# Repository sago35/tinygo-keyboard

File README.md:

# USB HID Keyboard firmware for TinyGo

**The API is not yet fixed.**  

The following are supported.  

* key input
    * squared matrix scan
    * matrix scan
    * duplex-matrix scan
    * rotary encoder
    * GPIO
    * UART
    * Shifter (tinygo.org/x/drivers/shifter)
* layer feature by mod key
* mouse click / mouse wheel
* support TRRS (UART)
* support [Vial](https://vial.rocks/)
    * Keymap
    * [Layers](https://get.vial.today/manual/layers.html) (MO(x), TO(x))
    * Matrix testers
    * [Macros](https://get.vial.today/manual/macros.html)
    * [Mod-Tap](https://docs.qmk.fm/mod_tap)
    * [Modifier Keys](https://docs.qmk.fm/feature_advanced_keycodes#modifier-keys)
    * [Combos](https://get.vial.today/manual/combos.html)

## Microcontrollers

The following microcontrollers are supported.  

* rp2040
* nrf52840
* samd51
* samd21
* mimxrt1062 (Teensy 4.0, requires the `teensy-flash` branch of tinygo-org/tinygo until it is merged)

## Tutorial

* [tutorial.md](./tutorial.md)

## Additional Resources

* [Create Your Own Keyboard with sago35/tinygo-keyboard (dev.to)](https://dev.to/sago35/create-your-own-keyboard-with-sago35tinygo-keyboard-4gbj)
* [自作キーボードをTinyGoで作る (Qiita, Japanese)](https://qiita.com/sago35/items/b008ed03cd403742e7aa)

## sgkb-0.4.0

```
# sgkb-0.4.0
$ tinygo flash --target xiao-rp2040 --size short --stack-size 8kb ./targets/sgkb/left/
$ tinygo flash --target xiao-rp2040 --size short --stack-size 8kb ./targets/sgkb/right/

# sgkb-0.3.0 or before
$ tinygo flash --target xiao-rp2040 --size short --stack-size 8kb ./targets/sgkb/left-0.3.0/
$ tinygo flash --target xiao-rp2040 --size short --stack-size 8kb ./targets/sgkb/right/
```

* files
    * [./kicad/sgkb](./kicad/sgkb/) for KiCad 7.0
        * KiCanvas : [sgkb-0.4.0 left](https://kicanvas.org/?github=https%3A%2F%2Fgithub.com%2Fsago35%2Ftinygo-keyboard%2Ftree%2Fsgkb-0.4.0-dev%2Fkicad%2Fsgkb%2Fsgkb)
        * KiCanvas : [sgkb-0.4.0 right](https://kicanvas.org/?github=https%3A%2F%2Fgithub.com%2Fsago35%2Ftinygo-keyboard%2Ftree%2Fmain%2Fkicad%2Fsgkb-right%2Fsgkb-right)
        * KiCanvas : [sgkb-0.3.0 left](https://kicanvas.org/?github=https%3A%2F%2Fgithub.com%2Fsago35%2Ftinygo-keyboard%2Ftree%2Fea336a62da237ce1e1972d8fc5d999a584e267c3%2Fkicad%2Fsgkb%2Fsgkb)
        * KiCanvas : [sgkb-0.3.0 right](https://kicanvas.org/?github=https%3A%2F%2Fgithub.com%2Fsago35%2Ftinygo-keyboard%2Ftree%2Fea336a62da237ce1e1972d8fc5d999a584e267c3%2Fkicad%2Fsgkb-right%2Fsgkb-right)

| name | amount |
| ---- | ------ |
| Cherry MX / Kailh Choc V1 | 72 |
| key cap (1u) | 68 |
| key cap (1.5u) | 1 |
| key cap (1.75u) | 1 |
| key cap (2u) | 1 |
| key cap (ISO-ENTER) | 1 |
| Stabilizer (2u) | 2 |
| diode 1N4148 | 72 |
| xiao-rp2040 | 2 |
| pin header 1x7 | 4 |
| TRRS connector | 2 |
| TRRS cable | 1 |

## sg48key

```
tinygo flash --target xiao --size short --stack-size 8kb ./targets/sg48key/
```

* files
    * [./kicad/sg48key](./kicad/sg48key/)
        * KiCanvas : [sg48key](https://kicanvas.org/?github=https%3A%2F%2Fgithub.com%2Fsago35%2Ftinygo-keyboard%2Ftree%2Fmain%2Fkicad%2Fsg48key%2Fsg48key)

## sgh60

```
tinygo flash --target waveshare-rp2040-zero --size short --stack-size 8kb ./targets/sgh60/
```

* files
    * [./kicad/sgh60](./kicad/sgh60/)
        * KiCanvas : [sgh60](https://kicanvas.org/?github=https%3A%2F%2Fgithub.com%2Fsago35%2Ftinygo-keyboard%2Ftree%2Fmain%2Fkicad%2Fsgh60%2Fsgh60)

## wiokey-0.1.0

```
$ tinygo flash --target wioterminal --size short --stack-size 8kb ./targets/wiokey/
```

* files
    * [./kicad/wiokey](./kicad/wiokey/) for KiCad 7.0
        * KiCanvas : [wiokey](https://kicanvas.org/?github=https%3A%2F%2Fgithub.com%2Fsago35%2Ftinygo-keyboard%2Ftree%2Fmain%2Fkicad%2Fwiokey%2Fwiokey)

| name | amount |
| ---- | ------ |
| Cherry MX / Kailh Choc V1 | 6 |
| key cap | 6 |
| diode 1N4148 | 6 |
| wioterminal | 1 |
| pin socket 2x20 | 2 |

## sgkey-0.1.0

```
$ tinygo flash --target xiao-rp2040 --size short --stack-size 8kb ./targets/sgkey/
```

* files
    * [./kicad/sgkey](./kicad/sgkey/) for KiCad 7.0
        * KiCanvas : [sgkey](https://kicanvas.org/?github=https%3A%2F%2Fgithub.com%2Fsago35%2Ftinygo-keyboard%2Ftree%2Fmain%2Fkicad%2Fsgkey%2Fsgkey)
* build guide
    * [./targets/sgkey/README.md](./targets/sgkey/README.md)

| name | amount |
| ---- | ------ |
| Cherry MX / Kailh Choc V1 | 6 |
| key cap | 6 |
| diode 1N4148 | 6 |
| xiao-rp2040 | 1 |
| i2c ssd1306 | 1 |
| register 10k ohm | 2 |

## fric10key-0.1.0

```
$ tinygo flash --target xiao-rp2040 --size short --stack-size 8kb ./targets/fric10key/
```

* files
    * [./kicad/fric10key](./kicad/fric10key/) for KiCad 7.0
        * KiCanvas : [fric10key](https://kicanvas.org/?github=https%3A%2F%2Fgithub.com%2Fsago35%2Ftinygo-keyboard%2Ftree%2Fmain%2Fkicad%2Ffric10key%2Ffric10key)

| name | amount |
| ---- | ------ |
| Cherry MX / Kailh Choc V1 | 27 |
| key cap (1u) | 26 |
| key cap (2u) | 1 |
| Stabilizer (2u) | 1 |
| diode 1N4148 | 27 |
| xiao-rp2040 | 1 |

## xiao-kb01

```
$ tinygo flash --target xiao-rp2040 --size short --stack-size 8kb ./targets/xiao-kb01/
```

* files
    * [./kicad/xiao-kb01](./kicad/xiao-kb01/) for KiCad 7.0
        * KiCanvas : [xiao-kb01](https://kicanvas.org/?github=https%3A%2F%2Fgithub.com%2Fsago35%2Ftinygo-keyboard%2Ftree%2Fmain%2Fkicad%2Fxiao-kb01%2Fxiao-kb01)

## Gopher Badge

```
$ tinygo flash --target gopher-badge --size short --stack-size 8kb ./targets/gopher-badge/
```

* schema
    * https://gopherbadge.com/

## GoBadge / PyBadge

```
$ tinygo flash --target gobadge --size short --stack-size 8kb ./targets/gobadge
```

* schema
    * https://learn.adafruit.com/adafruit-pybadge

## MacroPad RP2040

```
$ tinygo flash --target macropad-rp2040 --size short --stack-size 8kb ./targets/macropad-rp2040/
```

* schema
    * https://learn.adafruit.com/adafruit-macropad-rp2040/overview

## Teensy 4.0

A minimal 4-key GPIO keyboard for the Teensy 4.0.  
Connect pin 2 to pin 5 to GND to press a key. Pin 0 and pin 1 (UART1) stay free for debug output.  
USB HID and `machine.Flash` for the mimxrt1062 are only available on the `teensy-flash` branch of tinygo-org/tinygo for now.

```
$ tinygo flash --target teensy40 --size short --stack-size 8kb ./targets/teensy40/
```

## Restore default keymap

Set the key with the key code of `0x7C03`, and then press it.  
Then a reset will restore the default keymap.  
See [#8](https://github.com/sago35/tinygo-keyboard/pull/8).

## Restore default keymap (tinygo flash)

Restore default keymap each time it is reset by specifying `--tags reset_to_default`.  
Note that in this setting, any changes made from Vial or other sources will immediately revert to the original setting.  

```
$ tinygo flash --target wioterminal --size short  --tags reset_to_default ./targets/wiokey
```

## Note

* Basically, the `--stack-size 8kb` settings is required.
* If changing the version of tinygo-keyboard causes it to not work properly, please perform the `Restore default keymap` procedure.

## LICENSE

MIT

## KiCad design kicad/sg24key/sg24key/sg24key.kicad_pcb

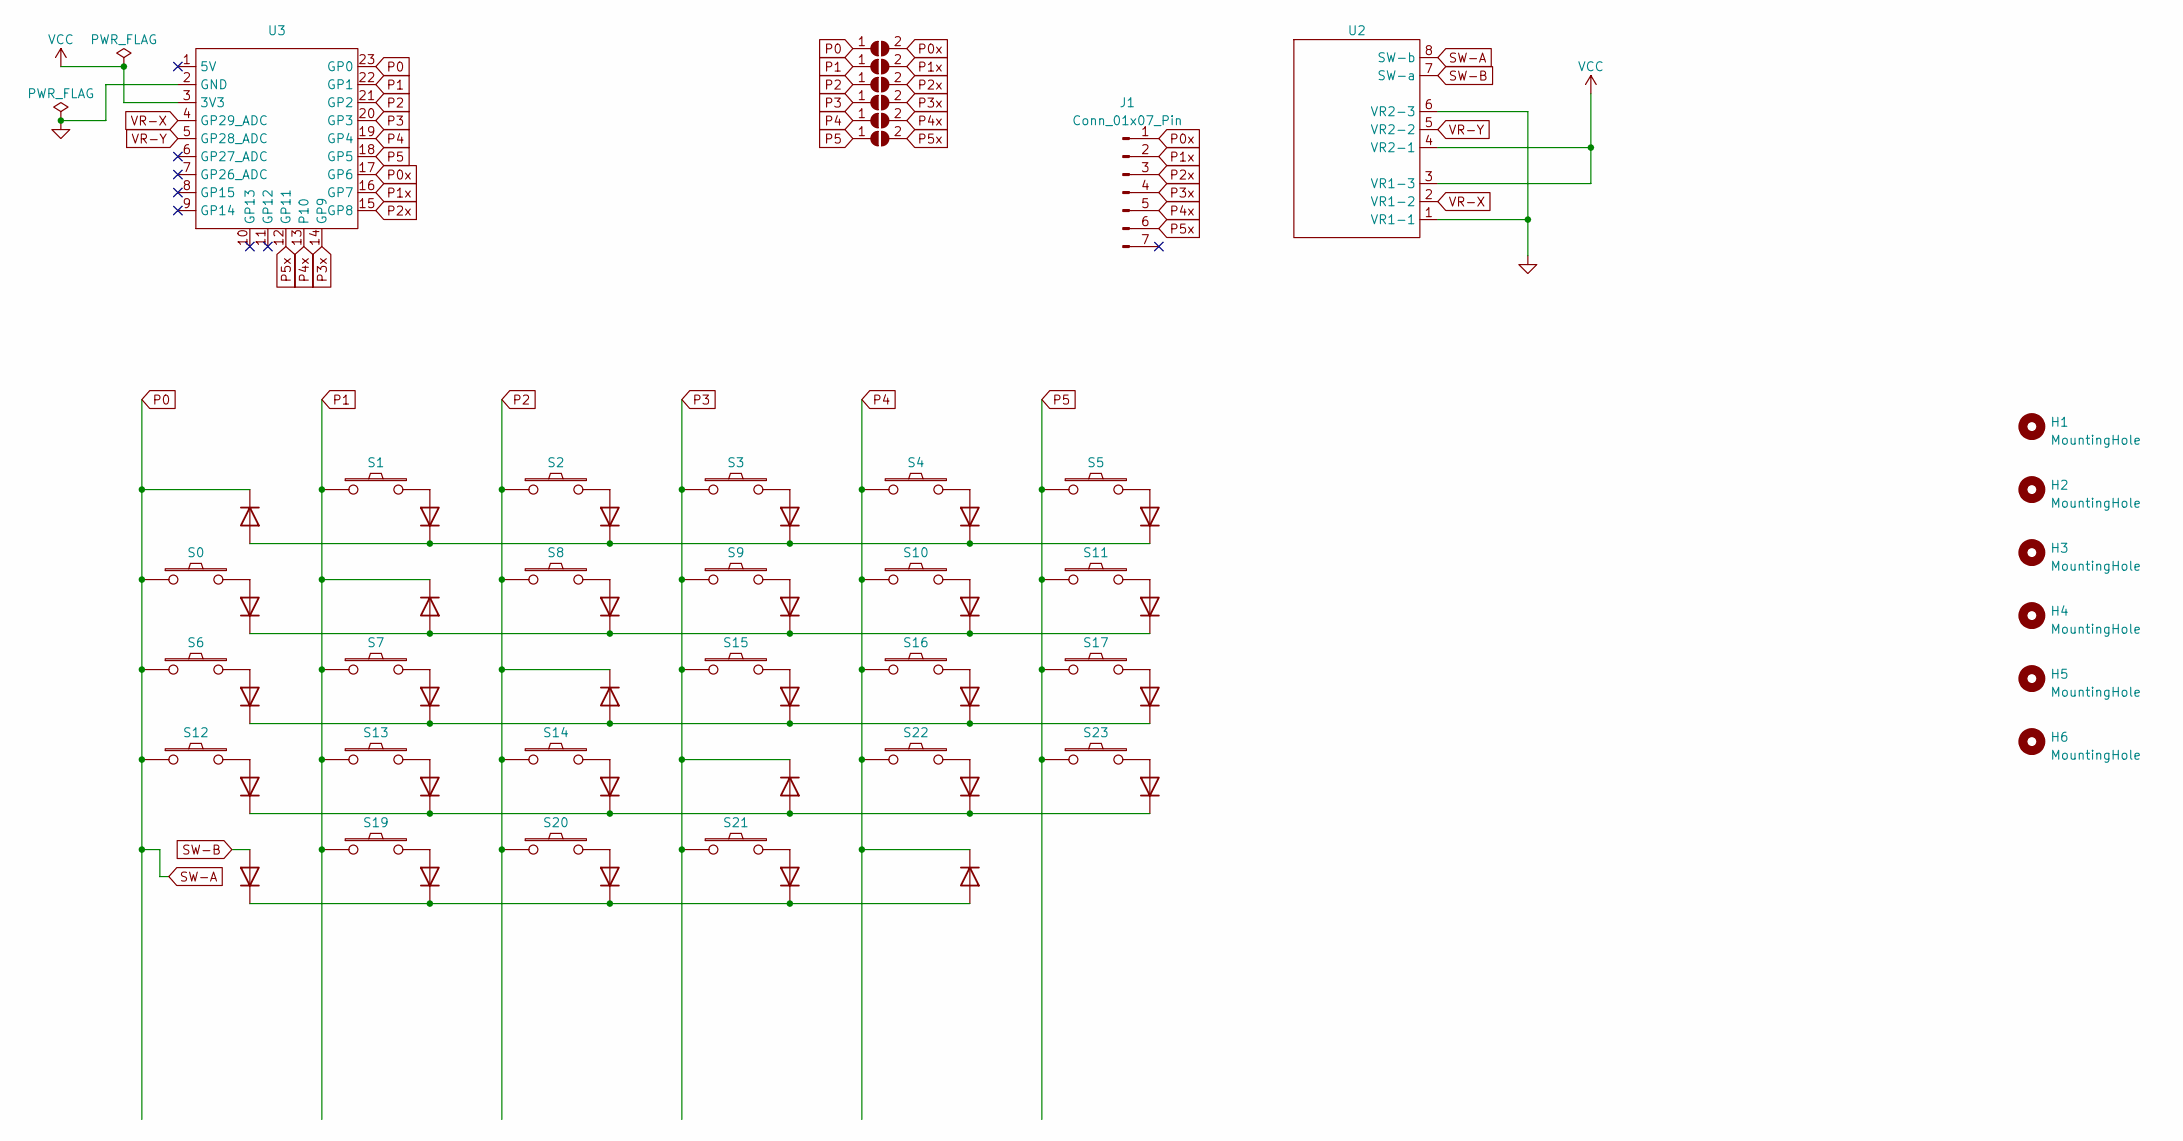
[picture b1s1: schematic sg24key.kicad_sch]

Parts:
D1, D2, D3, D9, D10, D11, D12, D17, D18, D19, D20, D22, D25, D26, D27, D28, D33, D34, D35, D36, D41, D42, D43, D44, D73, D74, D75, D76, D77: 1N4148; D3_SMD_v2
H1, H2, H3, H4, H5, H6: MountingHole; hole_2.5
J1: Conn_01x07_Pin; PinSocket_1x07_P2.54mm_Vertical
JP1, JP2, JP3, JP4, JP5, JP6: SolderJumper_2_Open; SolderJumper-2_P1.3mm_Open_Pad1.0x1.5mm
S0, S1, S2, S3, S4, S5, S6, S7, S8, S9, S10, S11, S12, S13, S14, S15, S16, S17, S19, S20, S21, S22, S23: SW_PUSH; CherryMX_Hotswap
U2: RKJXV122400R_CherryMX_Hotswap
U3: RP2040-Zero

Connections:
GND: U2.1 (VR1-1), U2.6 (VR2-3), U3.2 (GND)
unnamed: D1.2 (A), S0.2
unnamed: D1.1 (K), D18.1 (K), D26.1 (K), D34.1 (K), D42.1 (K), D74.2 (A)
unnamed: D2.2 (A), S6.2
unnamed: D3.2 (A), S12.2
unnamed: D9.2 (A), S1.2
unnamed: D10.2 (A), S7.2
unnamed: D2.1 (K), D10.1 (K), D27.1 (K), D35.1 (K), D43.1 (K), D75.2 (A)
unnamed: D11.2 (A), S13.2
unnamed: D3.1 (K), D11.1 (K), D19.1 (K), D36.1 (K), D44.1 (K), D76.2 (A)
unnamed: D12.2 (A), S19.2
unnamed: D12.1 (K), D20.1 (K), D22.1 (K), D28.1 (K), D77.2 (A)
unnamed: D17.2 (A), S2.2
unnamed: D9.1 (K), D17.1 (K), D25.1 (K), D33.1 (K), D41.1 (K), D73.2 (A)
unnamed: D18.2 (A), S8.2
unnamed: D19.2 (A), S14.2
unnamed: D20.2 (A), S20.2
unnamed: D25.2 (A), S3.2
unnamed: D26.2 (A), S9.2
unnamed: D27.2 (A), S15.2
unnamed: D28.2 (A), S21.2
unnamed: D33.2 (A), S4.2
unnamed: D34.2 (A), S10.2
unnamed: D35.2 (A), S16.2
unnamed: D36.2 (A), S22.2
unnamed: D41.2 (A), S5.2
unnamed: D42.2 (A), S11.2
unnamed: D43.2 (A), S17.2
unnamed: D44.2 (A), S23.2
P0: D73.1 (K), JP1.1 (A), S0.1, S6.1, S12.1, U2.8 (SW-b), U3.23 (GP0)
P0x: J1.1, JP1.2 (B), U3.17 (GP6)
P1: D74.1 (K), JP2.1 (A), S1.1, S7.1, S13.1, S19.1, U3.22 (GP1)
P1x: J1.2, JP2.2 (B), U3.16 (GP7)
P2: D75.1 (K), JP3.1 (A), S2.1, S8.1, S14.1, S20.1, U3.21 (GP2)
P2x: J1.3, JP3.2 (B), U3.15 (GP8)
P3: D76.1 (K), JP4.1 (A), S3.1, S9.1, S15.1, S21.1, U3.20 (GP3)
P3x: J1.4, JP4.2 (B), U3.14 (GP9)
P4: D77.1 (K), JP5.1 (A), S4.1, S10.1, S16.1, S22.1, U3.19 (GP4)
P4x: J1.5, JP5.2 (B), U3.13 (P10)
P5: JP6.1 (A), S5.1, S11.1, S17.1, S23.1, U3.18 (GP5)
P5x: J1.6, JP6.2 (B), U3.12 (GP11)
SW-B: D22.2 (A), U2.7 (SW-a)
VCC: U2.3 (VR1-3), U2.4 (VR2-1), U3.3 (3V3)
VR-X: U2.2 (VR1-2), U3.4 (GP29_ADC)
VR-Y: U2.5 (VR2-2), U3.5 (GP28_ADC)

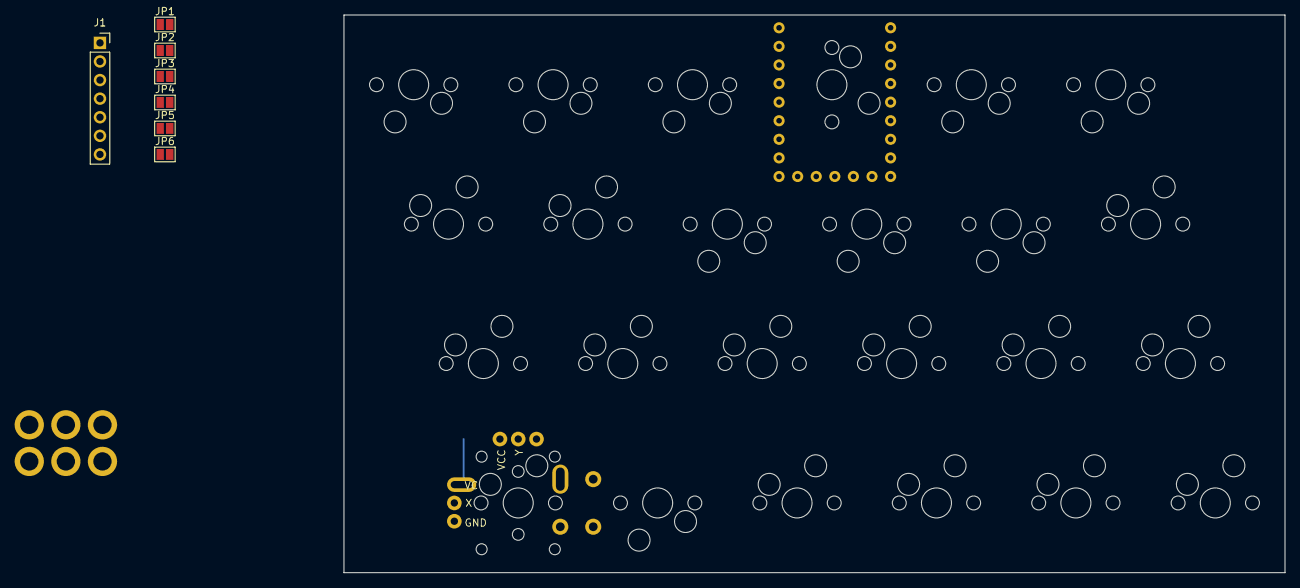
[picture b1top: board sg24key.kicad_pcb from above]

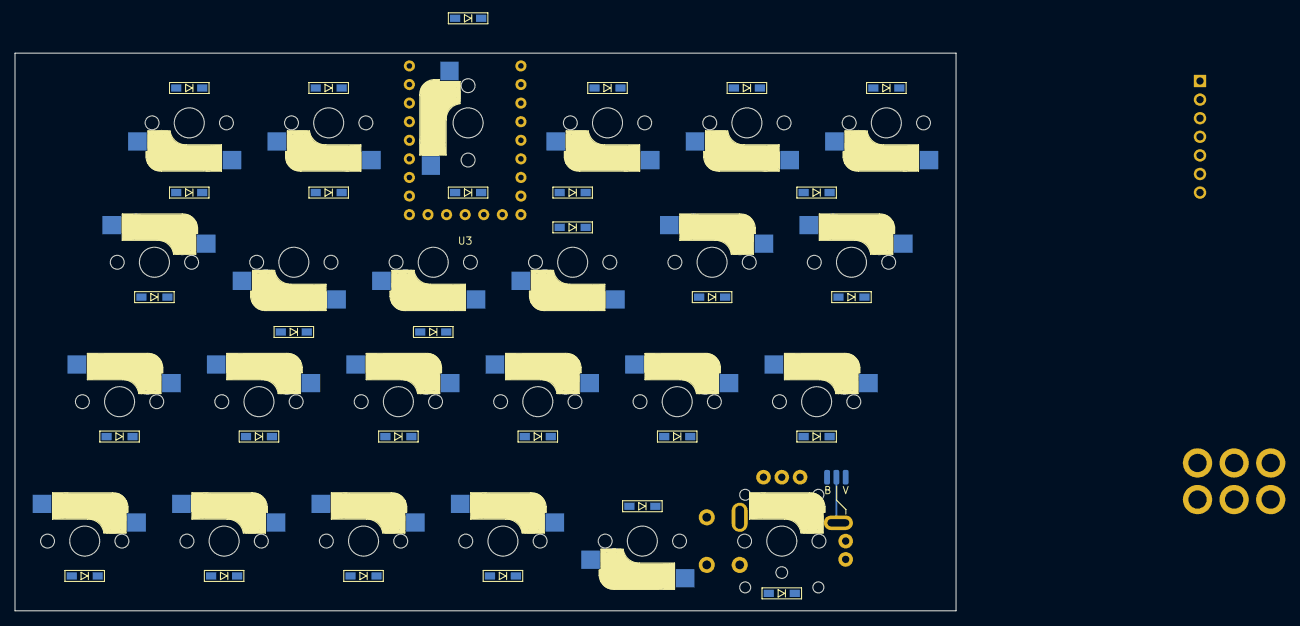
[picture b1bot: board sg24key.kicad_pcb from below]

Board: 2 copper layers, 128.6 x 76.2 mm, 67 parts (30 on the bottom side), 45 nets.

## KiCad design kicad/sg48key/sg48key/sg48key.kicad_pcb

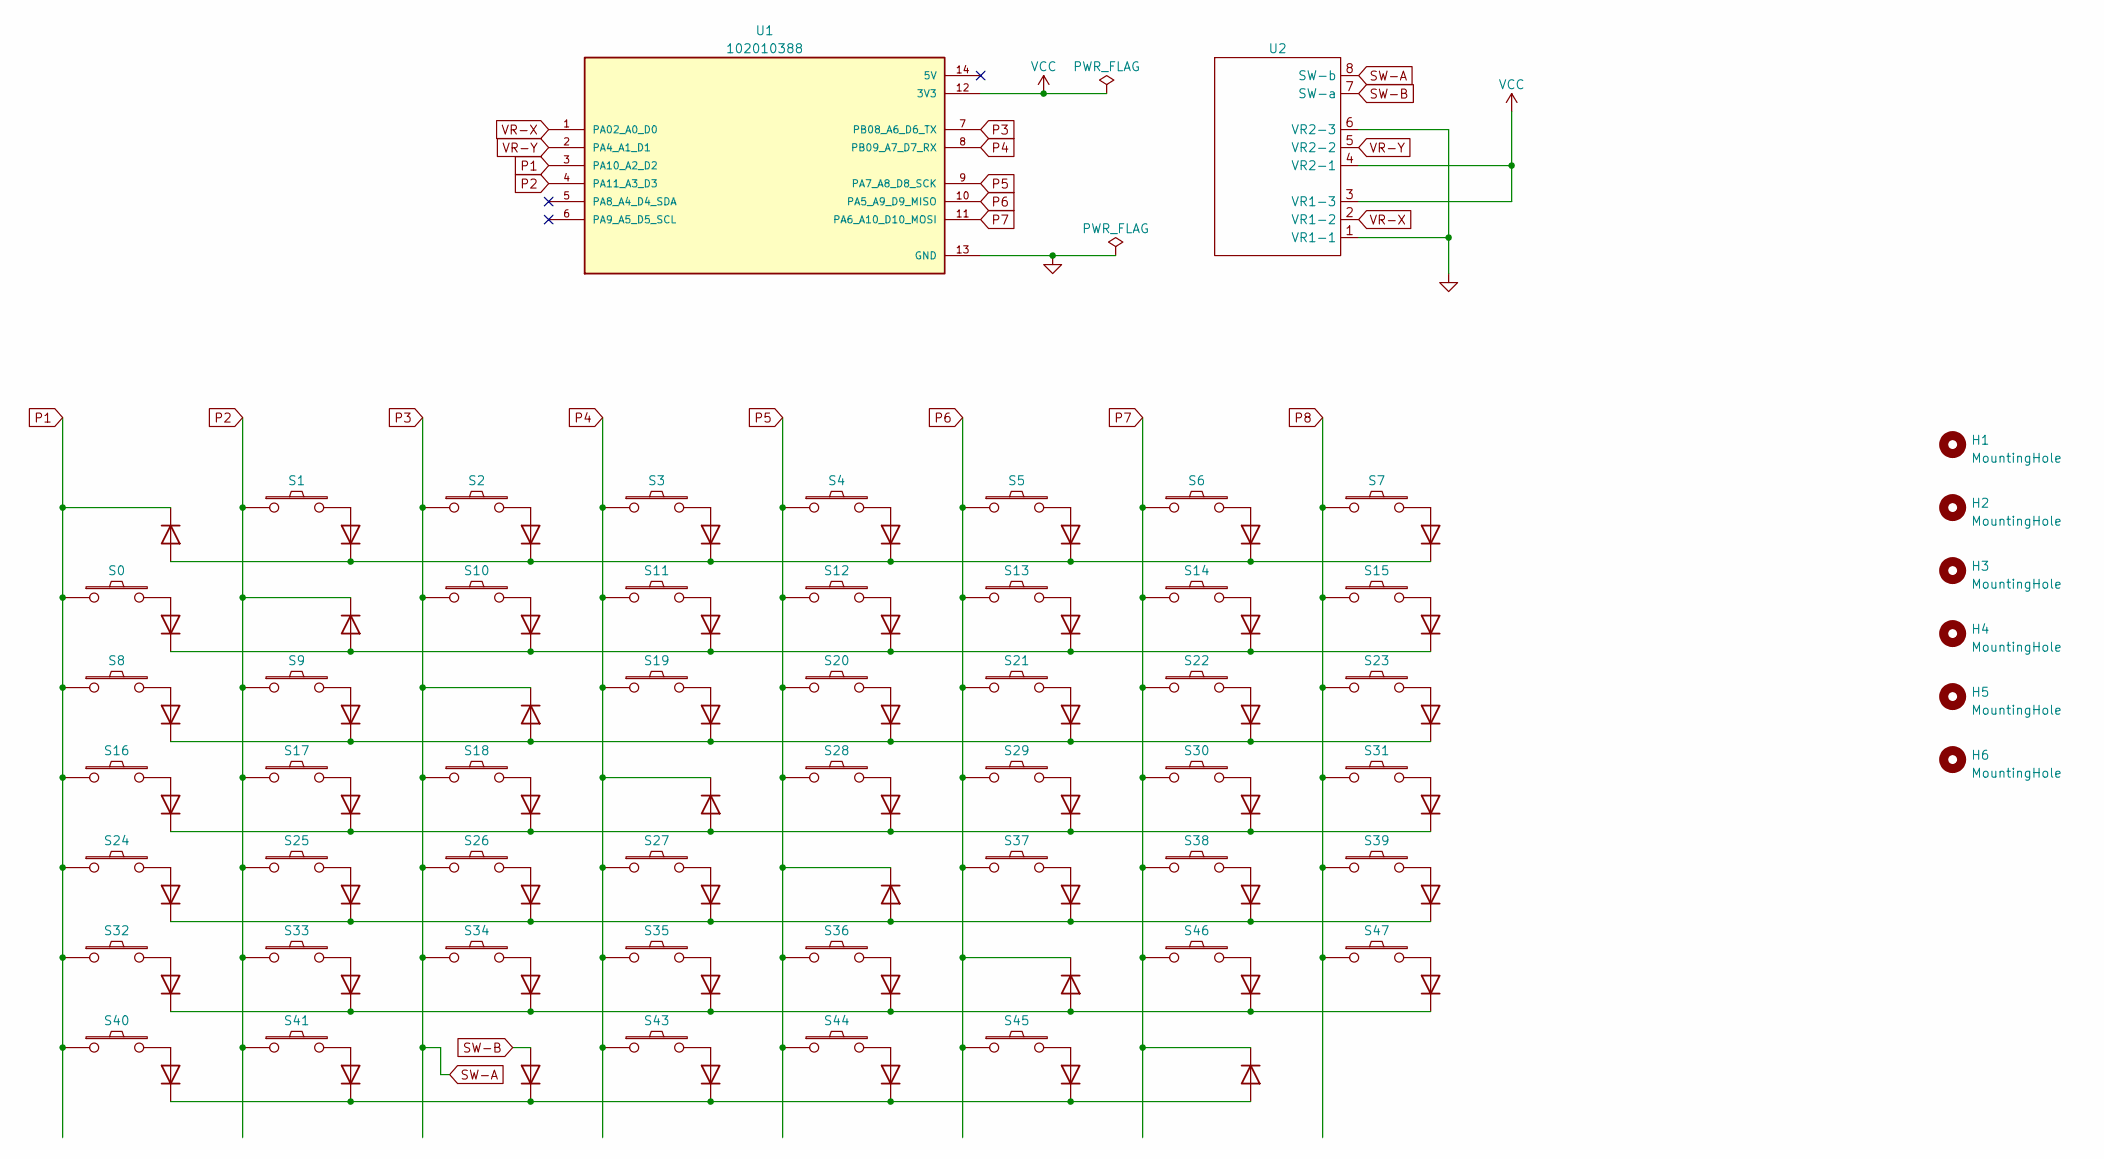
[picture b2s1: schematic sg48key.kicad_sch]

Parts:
D1, D2, D3, D4, D5, D6, D9, D10, D11, D12, D13, D14, D17, D18, D19, D20, D21, D22, D25, D26, D27, D28, D29, D30, D33, D34, D35, D36, D37, D38, D41, D42, D43, D44, D45, D46, D49, D50, D51, D52, D53, D54, D57, D58, D59, D60, D61, D62, D73, D74, D75, D76, D77, D78, D79: 1N4148; D3_SMD_v2
H1, H2, H3, H4, H5, H6: MountingHole; hole_2.5
S0, S1, S2, S3, S4, S5, S6, S7, S8, S9, S10, S11, S12, S13, S14, S15, S16, S17, S18, S19, S20, S21, S22, S23, S24, S25, S26, S27, S28, S29, S30, S31, S32, S33, S34, S35, S36, S37, S38, S39, S40, S41, S43, S44, S45, S46, S47: SW_PUSH; CherryMX_Hotswap
U1: 102010388; MODULE_102010388; PARTREV N/A
U2: RKJXV122400R

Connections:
GND: U1.13 (GND), U2.1 (VR1-1), U2.6 (VR2-3)
unnamed: D1.2 (A), S0.2
unnamed: D1.1 (K), D18.1 (K), D26.1 (K), D34.1 (K), D42.1 (K), D50.1 (K), D58.1 (K), D74.2 (A)
unnamed: D2.2 (A), S8.2
unnamed: D3.2 (A), S16.2
unnamed: D4.2 (A), S24.2
unnamed: D5.2 (A), S32.2
unnamed: D6.2 (A), S40.2
unnamed: D9.2 (A), S1.2
unnamed: D10.2 (A), S9.2
unnamed: D2.1 (K), D10.1 (K), D27.1 (K), D35.1 (K), D43.1 (K), D51.1 (K), D59.1 (K), D75.2 (A)
unnamed: D11.2 (A), S17.2
unnamed: D3.1 (K), D11.1 (K), D19.1 (K), D36.1 (K), D44.1 (K), D52.1 (K), D60.1 (K), D76.2 (A)
unnamed: D12.2 (A), S25.2
unnamed: D4.1 (K), D12.1 (K), D20.1 (K), D28.1 (K), D45.1 (K), D53.1 (K), D61.1 (K), D77.2 (A)
unnamed: D13.2 (A), S33.2
unnamed: D5.1 (K), D13.1 (K), D21.1 (K), D29.1 (K), D37.1 (K), D54.1 (K), D62.1 (K), D78.2 (A)
unnamed: D14.2 (A), S41.2
unnamed: D6.1 (K), D14.1 (K), D22.1 (K), D30.1 (K), D38.1 (K), D46.1 (K), D79.2 (A)
unnamed: D17.2 (A), S2.2
unnamed: D9.1 (K), D17.1 (K), D25.1 (K), D33.1 (K), D41.1 (K), D49.1 (K), D57.1 (K), D73.2 (A)
unnamed: D18.2 (A), S10.2
unnamed: D19.2 (A), S18.2
unnamed: D20.2 (A), S26.2
unnamed: D21.2 (A), S34.2
unnamed: D25.2 (A), S3.2
unnamed: D26.2 (A), S11.2
unnamed: D27.2 (A), S19.2
unnamed: D28.2 (A), S27.2
unnamed: D29.2 (A), S35.2
unnamed: D30.2 (A), S43.2
unnamed: D33.2 (A), S4.2
unnamed: D34.2 (A), S12.2
unnamed: D35.2 (A), S20.2
unnamed: D36.2 (A), S28.2
unnamed: D37.2 (A), S36.2
unnamed: D38.2 (A), S44.2
unnamed: D41.2 (A), S5.2
unnamed: D42.2 (A), S13.2
unnamed: D43.2 (A), S21.2
unnamed: D44.2 (A), S29.2
unnamed: D45.2 (A), S37.2
unnamed: D46.2 (A), S45.2
unnamed: D49.2 (A), S6.2
unnamed: D50.2 (A), S14.2
unnamed: D51.2 (A), S22.2
unnamed: D52.2 (A), S30.2
unnamed: D53.2 (A), S38.2
unnamed: D54.2 (A), S46.2
unnamed: D57.2 (A), S7.2
unnamed: D58.2 (A), S15.2
unnamed: D59.2 (A), S23.2
unnamed: D60.2 (A), S31.2
unnamed: D61.2 (A), S39.2
unnamed: D62.2 (A), S47.2
P1: D73.1 (K), S0.1, S8.1, S16.1, S24.1, S32.1, S40.1, U1.3 (PA10_A2_D2)
P2: D74.1 (K), S1.1, S9.1, S17.1, S25.1, S33.1, S41.1, U1.4 (PA11_A3_D3)
P3: D75.1 (K), S2.1, S10.1, S18.1, S26.1, S34.1, U1.7 (PB08_A6_D6_TX), U2.8 (SW-b)
P4: D76.1 (K), S3.1, S11.1, S19.1, S27.1, S35.1, S43.1, U1.8 (PB09_A7_D7_RX)
P5: D77.1 (K), S4.1, S12.1, S20.1, S28.1, S36.1, S44.1, U1.9 (PA7_A8_D8_SCK)
P6: D78.1 (K), S5.1, S13.1, S21.1, S29.1, S37.1, S45.1, U1.10 (PA5_A9_D9_MISO)
P7: D79.1 (K), S6.1, S14.1, S22.1, S30.1, S38.1, S46.1, U1.11 (PA6_A10_D10_MOSI)
P8: S7.1, S15.1, S23.1, S31.1, S39.1, S47.1
SW-B: D22.2 (A), U2.7 (SW-a)
VCC: U1.12 (3V3), U2.3 (VR1-3), U2.4 (VR2-1)
VR-X: U1.1 (PA02_A0_D0), U2.2 (VR1-2)
VR-Y: U1.2 (PA4_A1_D1), U2.5 (VR2-2)

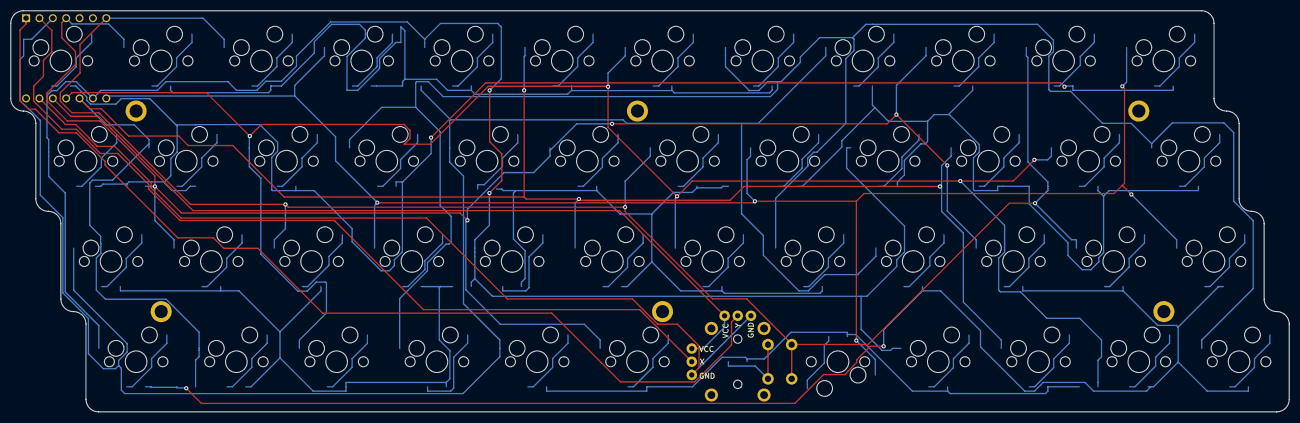
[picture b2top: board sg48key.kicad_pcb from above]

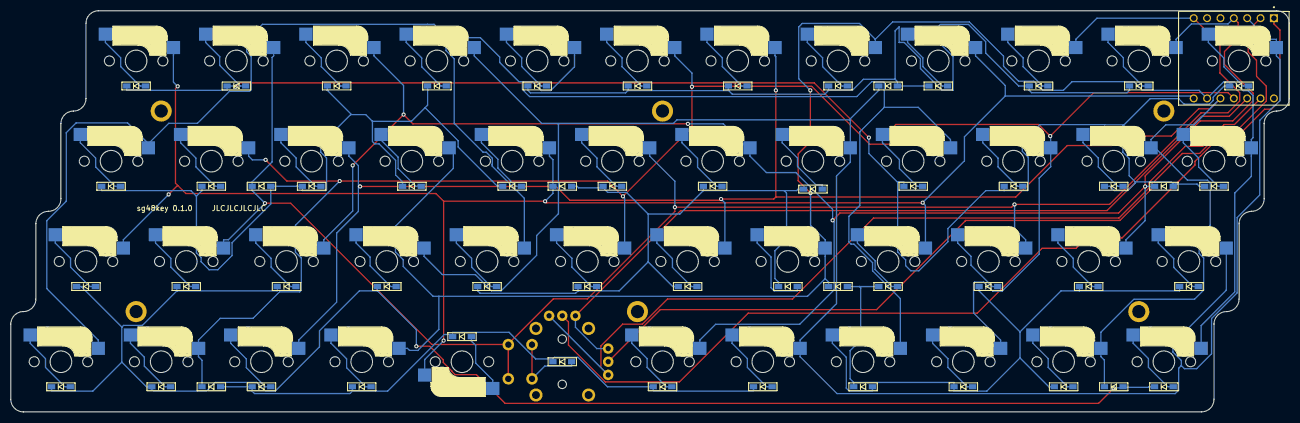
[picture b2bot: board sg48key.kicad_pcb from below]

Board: 2 copper layers, 242.9 x 76.2 mm, 110 parts (56 on the bottom side), 67 nets.

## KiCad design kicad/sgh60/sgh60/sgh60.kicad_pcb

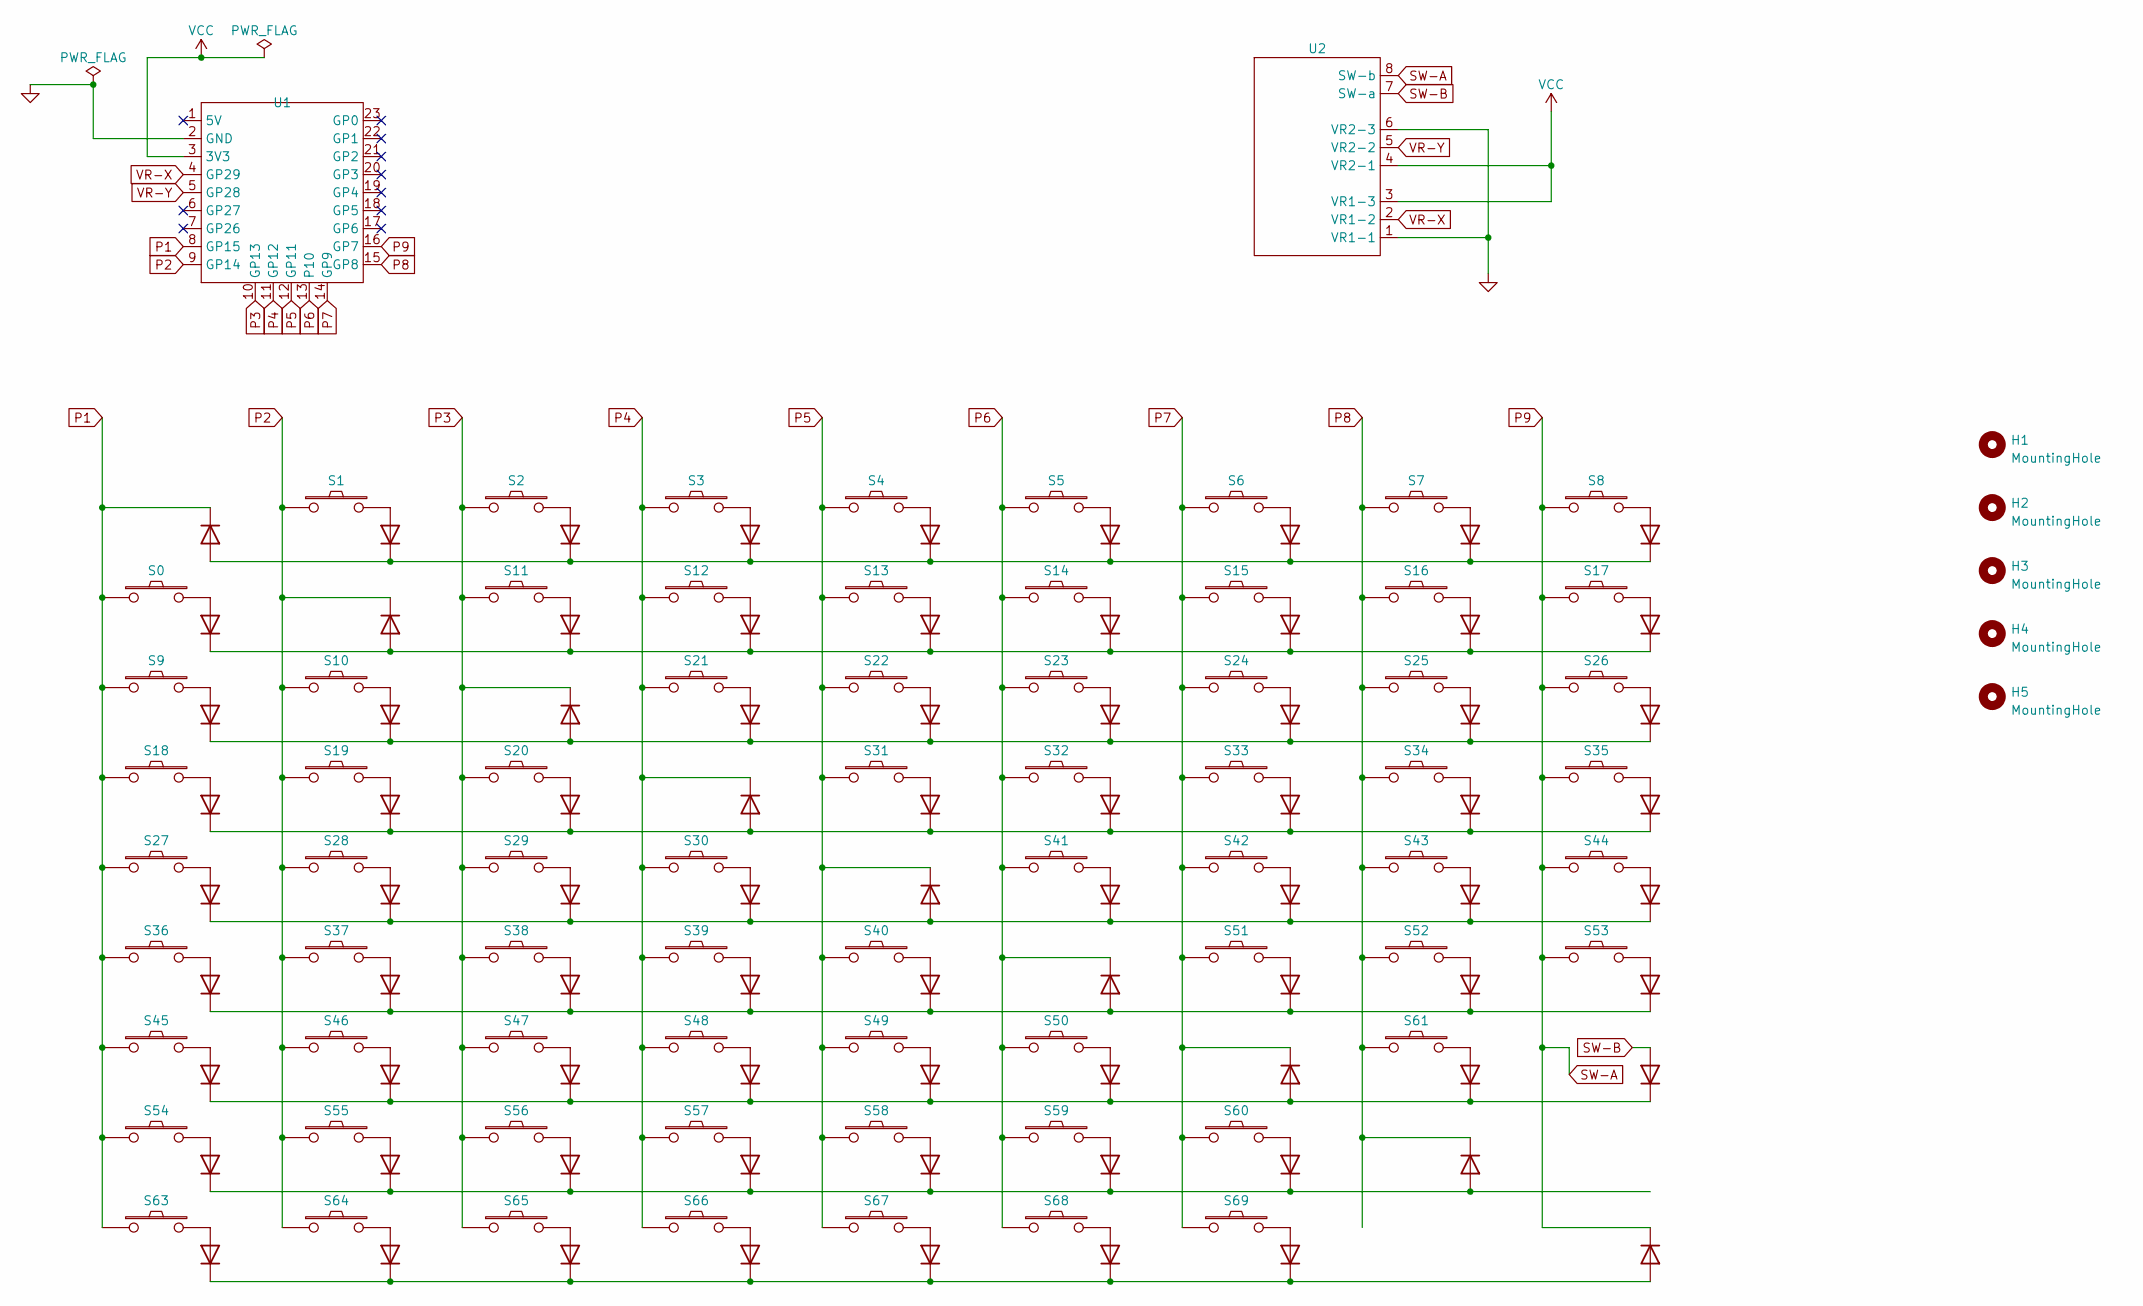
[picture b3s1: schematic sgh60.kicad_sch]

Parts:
D1, D2, D3, D4, D5, D6, D7, D8, D9, D10, D11, D12, D13, D14, D15, D16, D17, D18, D19, D20, D21, D22, D23, D24, D25, D26, D27, D28, D29, D30, D31, D32, D33, D34, D35, D36, D37, D38, D39, D40, D41, D42, D43, D44, D45, D46, D47, D48, D49, D50, D51, D52, D53, D54, D55, D56, D57, D58, D59, D60, D61, D62, D63, D65, D66, D67, D68, D69, D70, D71, D73, D74, D75, D76, D77, D78, D79, D80, D81: 1N4148; D3_SMD_v2
H1, H2, H3: MountingHole; hole_2.5
H4, H5: MountingHole; hole_7x3
S0, S1, S2, S3, S4, S5, S6, S7, S8, S9, S10, S11, S12, S13, S14, S15, S16, S17, S18, S19, S20, S21, S22, S23, S24, S25, S26, S27, S29, S30, S31, S32, S33, S34, S35, S36, S37, S38, S39, S40, S41, S43, S44, S45, S46, S47, S48, S49, S50, S51, S52, S53, S54, S55, S56, S57, S58, S59, S60, S61, S63, S64, S65, S66, S67, S68, S69: SW_PUSH; CherryMX_Hotswap
S28: SW_PUSH; CherryMX_Hotswap_with_ISO_Enter_stabilizer
S42: SW_PUSH; CherryMX_Hotswap_with_2u_stabilizer
U1: RP2040-Zero_reverse_for_sgh60
U2: RKJXV122400R

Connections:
GND: U1.2 (GND), U2.1 (VR1-1), U2.6 (VR2-3)
unnamed: D1.2 (A), S0.2
unnamed: D1.1 (K), D18.1 (K), D26.1 (K), D34.1 (K), D42.1 (K), D50.1 (K), D58.1 (K), D66.1 (K), D74.2 (A)
unnamed: D2.2 (A), S9.2
unnamed: D3.2 (A), S18.2
unnamed: D4.2 (A), S27.2
unnamed: D5.2 (A), S36.2
unnamed: D6.2 (A), S45.2
unnamed: D7.2 (A), S54.2
unnamed: D8.2 (A), S63.2
unnamed: D9.2 (A), S1.2
unnamed: D10.2 (A), S10.2
unnamed: D2.1 (K), D10.1 (K), D27.1 (K), D35.1 (K), D43.1 (K), D51.1 (K), D59.1 (K), D67.1 (K), D75.2 (A)
unnamed: D11.2 (A), S19.2
unnamed: D3.1 (K), D11.1 (K), D19.1 (K), D36.1 (K), D44.1 (K), D52.1 (K), D60.1 (K), D68.1 (K), D76.2 (A)
unnamed: D12.2 (A), S28.2
unnamed: D4.1 (K), D12.1 (K), D20.1 (K), D28.1 (K), D45.1 (K), D53.1 (K), D61.1 (K), D69.1 (K), D77.2 (A)
unnamed: D13.2 (A), S37.2
unnamed: D5.1 (K), D13.1 (K), D21.1 (K), D29.1 (K), D37.1 (K), D54.1 (K), D62.1 (K), D70.1 (K), D78.2 (A)
unnamed: D14.2 (A), S46.2
unnamed: D6.1 (K), D14.1 (K), D22.1 (K), D30.1 (K), D38.1 (K), D46.1 (K), D63.1 (K), D71.1 (K), D79.2 (A)
unnamed: D15.2 (A), S55.2
unnamed: D7.1 (K), D15.1 (K), D23.1 (K), D31.1 (K), D39.1 (K), D47.1 (K), D55.1 (K), D80.2 (A)
unnamed: D16.2 (A), S64.2
unnamed: D8.1 (K), D16.1 (K), D24.1 (K), D32.1 (K), D40.1 (K), D48.1 (K), D56.1 (K), D81.2 (A)
unnamed: D17.2 (A), S2.2
unnamed: D9.1 (K), D17.1 (K), D25.1 (K), D33.1 (K), D41.1 (K), D49.1 (K), D57.1 (K), D65.1 (K), D73.2 (A)
unnamed: D18.2 (A), S11.2
unnamed: D19.2 (A), S20.2
unnamed: D20.2 (A), S29.2
unnamed: D21.2 (A), S38.2
unnamed: D22.2 (A), S47.2
unnamed: D23.2 (A), S56.2
unnamed: D24.2 (A), S65.2
unnamed: D25.2 (A), S3.2
unnamed: D26.2 (A), S12.2
unnamed: D27.2 (A), S21.2
unnamed: D28.2 (A), S30.2
unnamed: D29.2 (A), S39.2
unnamed: D30.2 (A), S48.2
unnamed: D31.2 (A), S57.2
unnamed: D32.2 (A), S66.2
unnamed: D33.2 (A), S4.2
unnamed: D34.2 (A), S13.2
unnamed: D35.2 (A), S22.2
unnamed: D36.2 (A), S31.2
unnamed: D37.2 (A), S40.2
unnamed: D38.2 (A), S49.2
unnamed: D39.2 (A), S58.2
unnamed: D40.2 (A), S67.2
unnamed: D41.2 (A), S5.2
unnamed: D42.2 (A), S14.2
unnamed: D43.2 (A), S23.2
unnamed: D44.2 (A), S32.2
unnamed: D45.2 (A), S41.2
unnamed: D46.2 (A), S50.2
unnamed: D47.2 (A), S59.2
unnamed: D48.2 (A), S68.2
unnamed: D49.2 (A), S6.2
unnamed: D50.2 (A), S15.2
unnamed: D51.2 (A), S24.2
unnamed: D52.2 (A), S33.2
unnamed: D53.2 (A), S42.2
unnamed: D54.2 (A), S51.2
unnamed: D55.2 (A), S60.2
unnamed: D56.2 (A), S69.2
unnamed: D57.2 (A), S7.2
unnamed: D58.2 (A), S16.2
unnamed: D59.2 (A), S25.2
unnamed: D60.2 (A), S34.2
unnamed: D61.2 (A), S43.2
unnamed: D62.2 (A), S52.2
unnamed: D63.2 (A), S61.2
unnamed: D65.2 (A), S8.2
unnamed: D66.2 (A), S17.2
unnamed: D67.2 (A), S26.2
unnamed: D68.2 (A), S35.2
unnamed: D69.2 (A), S44.2
unnamed: D70.2 (A), S53.2
P1: D73.1 (K), S0.1, S9.1, S18.1, S27.1, S36.1, S45.1, S54.1, S63.1, U1.8 (GP15)
P2: D74.1 (K), S1.1, S10.1, S19.1, S28.1, S37.1, S46.1, S55.1, S64.1, U1.9 (GP14)
P3: D75.1 (K), S2.1, S11.1, S20.1, S29.1, S38.1, S47.1, S56.1, S65.1, U1.10 (GP13)
P4: D76.1 (K), S3.1, S12.1, S21.1, S30.1, S39.1, S48.1, S57.1, S66.1, U1.11 (GP12)
P5: D77.1 (K), S4.1, S13.1, S22.1, S31.1, S40.1, S49.1, S58.1, S67.1, U1.12 (GP11)
P6: D78.1 (K), S5.1, S14.1, S23.1, S32.1, S41.1, S50.1, S59.1, S68.1, U1.13 (P10)
P7: D79.1 (K), S6.1, S15.1, S24.1, S33.1, S42.1, S51.1, S60.1, S69.1, U1.14 (GP9)
P8: D80.1 (K), S7.1, S16.1, S25.1, S34.1, S43.1, S52.1, S61.1, U1.15 (GP8)
P9: D81.1 (K), S8.1, S17.1, S26.1, S35.1, S44.1, S53.1, U1.16 (GP7), U2.8 (SW-b)
SW-B: D71.2 (A), U2.7 (SW-a)
VCC: U1.3 (3V3), U2.3 (VR1-3), U2.4 (VR2-1)
VR-X: U1.4 (GP29), U2.2 (VR1-2)
VR-Y: U1.5 (GP28), U2.5 (VR2-2)

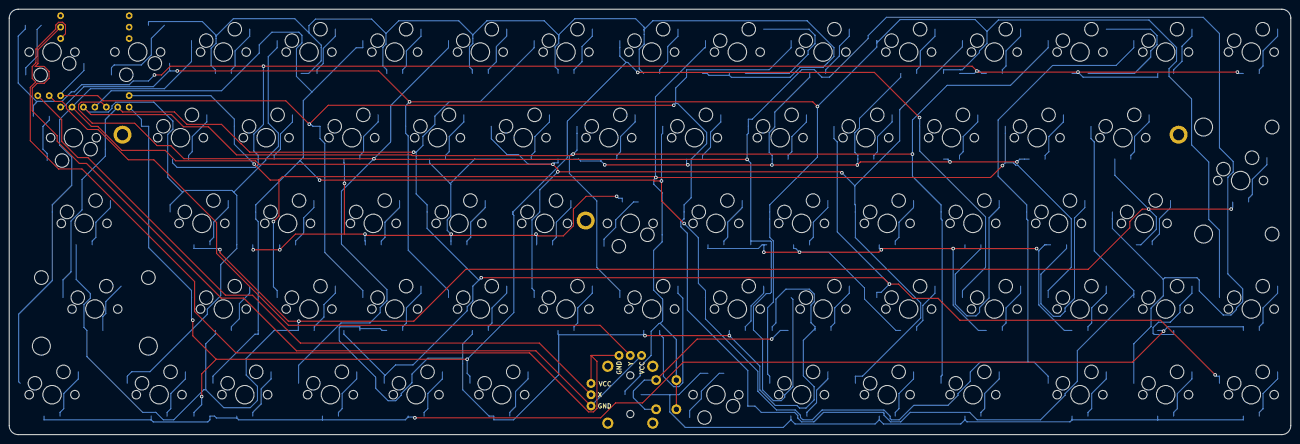
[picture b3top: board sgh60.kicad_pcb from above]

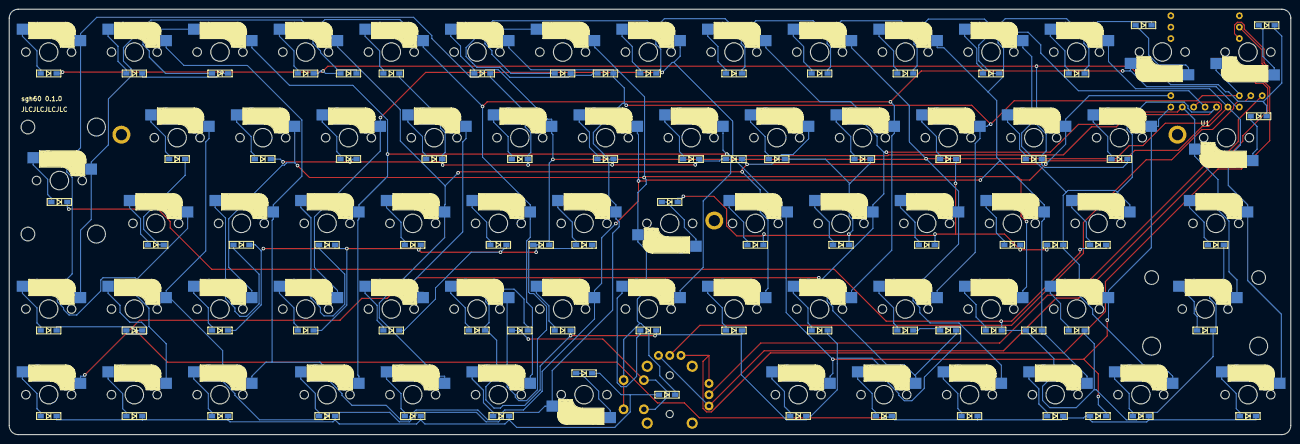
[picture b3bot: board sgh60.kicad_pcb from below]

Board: 2 copper layers, 285.0 x 94.6 mm, 155 parts (80 on the bottom side), 92 nets.
